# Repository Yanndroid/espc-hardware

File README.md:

# ESP Clock

ESPC stands for [ESP](https://www.espressif.com/) Clock and is a digital IoT clock. It's connected to WiFi, automatically syncs time, shows weather information, and most importantly, has RGB! At its core, there is an ESP8266, and the display is made of WS2812B LEDs.  
It's a project I've been working on over the past few years, and it has allowed me to learn a lot about the C language and PCB designs.

This project consists of multiple repositories:

- [espc-firmware](https://github.com/Yanndroid/espc-firmware)
- espc-hardware
- [espc-python-client](https://github.com/Yanndroid/espc-python-client)
- [espc-dev-tools](https://github.com/Yanndroid/espc-dev-tools)

# ESP Clock Hardware

This repository contains the PCB and 3d models for the ESPC.

### PCB

<div align="center">

</div>

### 3d Models

<div align="center">

</div>

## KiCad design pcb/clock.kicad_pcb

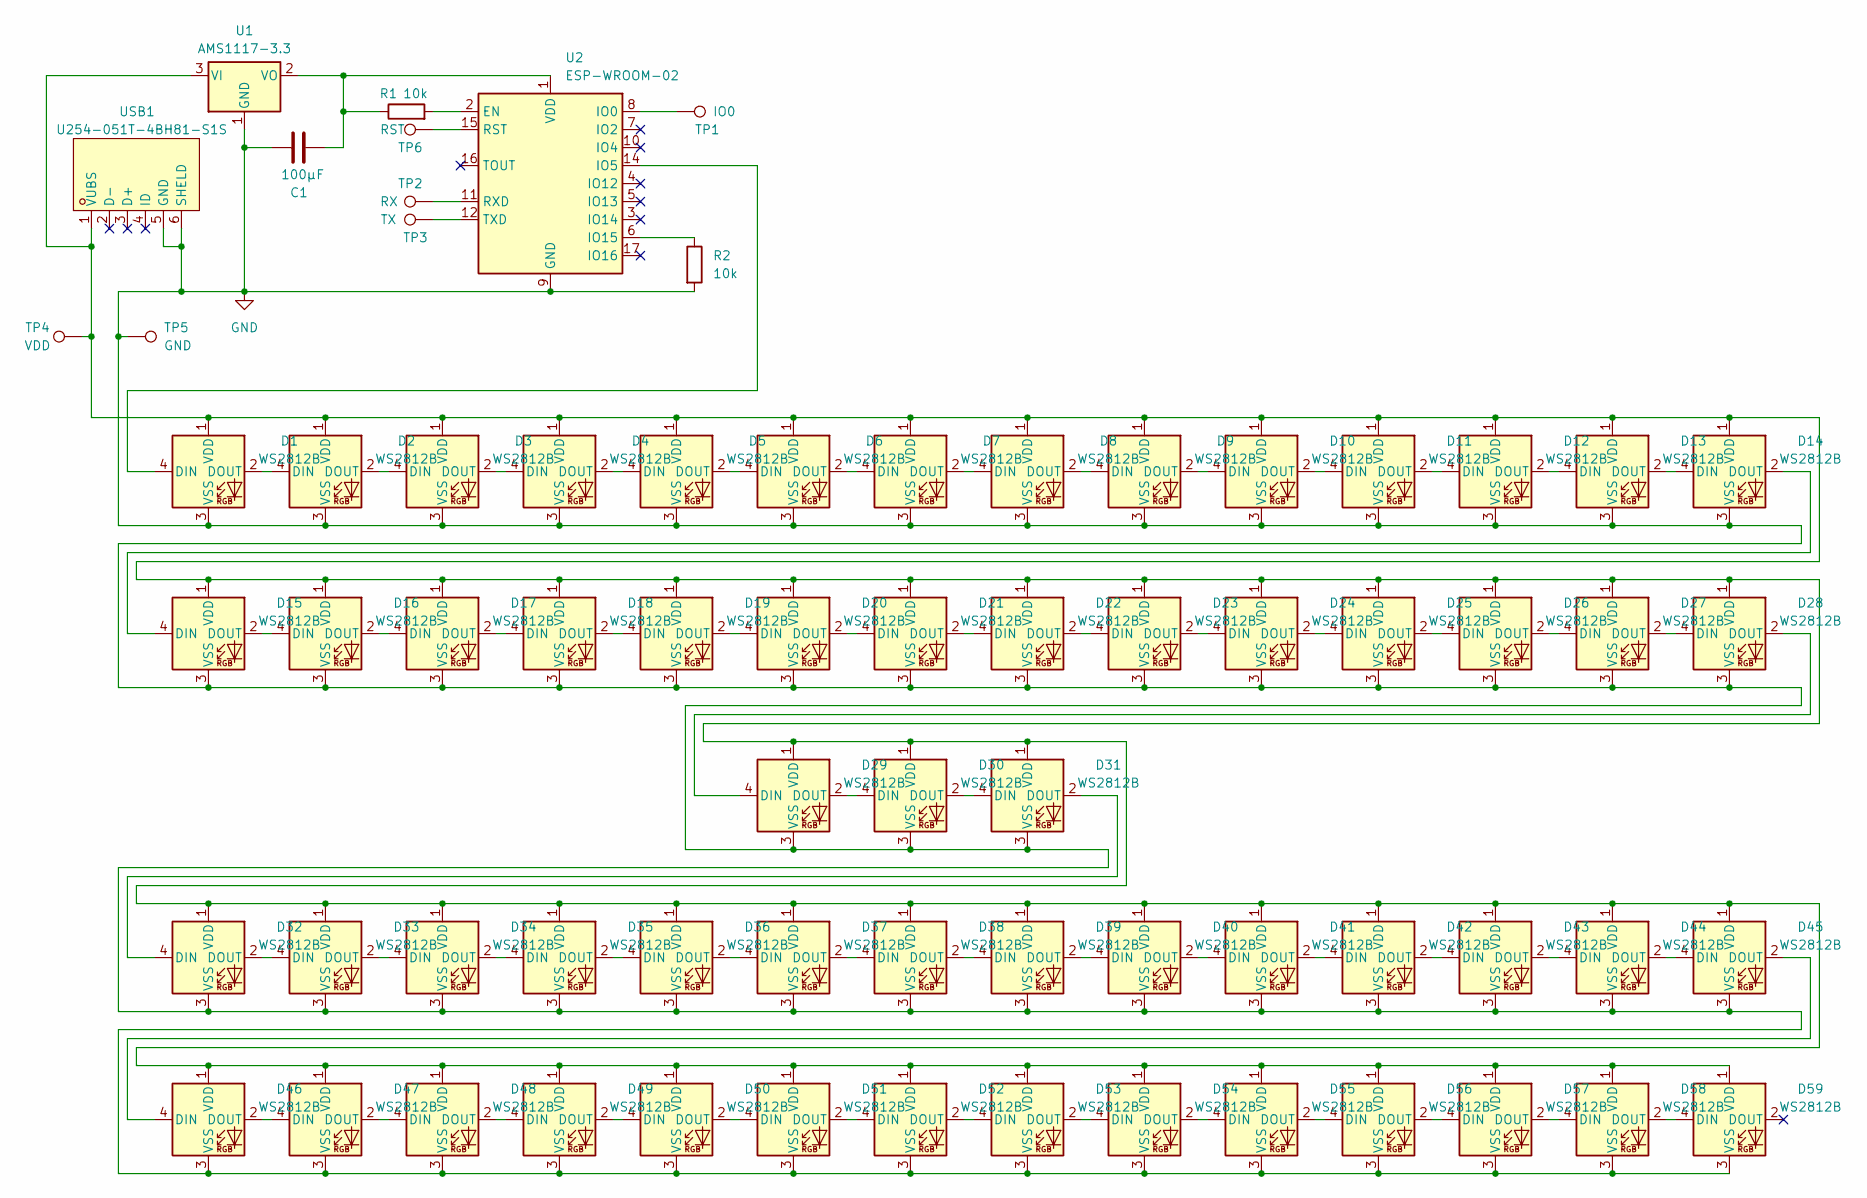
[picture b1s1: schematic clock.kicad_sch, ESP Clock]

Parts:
C1: 100µF; C_1206_3216Metric
D1, D2, D3, D4, D5, D6, D7, D8, D9, D10, D11, D12, D13, D14, D15, D16, D17, D18, D19, D20, D21, D22, D23, D24, D25, D26, D27, D28, D29, D30, D31, D32, D33, D34, D35, D36, D37, D38, D39, D40, D41, D42, D43, D44, D45, D46, D47, D48, D49, D50, D51, D52, D53, D54, D55, D56, D57, D58, D59: WS2812B; LED_WS2812B_PLCC4_5.0x5.0mm_P3.2mm
R1, R2: 10k; R_0603_1608Metric
TP1: IO0; TestPoint_Pad_D1.5mm
TP2: RX; TestPoint_Pad_D1.5mm
TP3: TX; TestPoint_Pad_D1.5mm
TP4: VDD; TestPoint_Pad_D2.5mm
TP5: GND; TestPoint_Pad_D2.5mm
TP6: RST; TestPoint_Pad_D1.5mm
U1: AMS1117-3.3; SOT-223-3_TabPin2
U2: ESP-WROOM-02
USB1: U254-051T-4BH81-S1S; MICRO-USB-SMD_U254-051T-4BH81-S1S; LCSC Part C2682232

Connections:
GND: C1.2, D1.3 (VSS), D2.3 (VSS), D3.3 (VSS), D4.3 (VSS), D5.3 (VSS), D6.3 (VSS), D7.3 (VSS), D8.3 (VSS), D9.3 (VSS), D10.3 (VSS), D11.3 (VSS), D12.3 (VSS), D13.3 (VSS), D14.3 (VSS), D15.3 (VSS), D16.3 (VSS), D17.3 (VSS), D18.3 (VSS), D19.3 (VSS), D20.3 (VSS), D21.3 (VSS), D22.3 (VSS), D23.3 (VSS), D24.3 (VSS), D25.3 (VSS), D26.3 (VSS), D27.3 (VSS), D28.3 (VSS), D29.3 (VSS), D30.3 (VSS), D31.3 (VSS), D32.3 (VSS), D33.3 (VSS), D34.3 (VSS), D35.3 (VSS), D36.3 (VSS), D37.3 (VSS), D38.3 (VSS), D39.3 (VSS), D40.3 (VSS), D41.3 (VSS), D42.3 (VSS), D43.3 (VSS), D44.3 (VSS), D45.3 (VSS), D46.3 (VSS), D47.3 (VSS), D48.3 (VSS), D49.3 (VSS), D50.3 (VSS), D51.3 (VSS), D52.3 (VSS), D53.3 (VSS), D54.3 (VSS), D55.3 (VSS), D56.3 (VSS), D57.3 (VSS), D58.3 (VSS), D59.3 (VSS), R2.2, TP5.1, U1.1 (GND), U2.9 (GND), U2.13 (GND), U2.18 (GND), U2.19 (GND), USB1.5 (GND), USB1.6 (SHELD)
unnamed: D1.4 (DIN), U2.14 (IO5)
unnamed: D1.2 (DOUT), D2.4 (DIN)
unnamed: D1.1 (VDD), D2.1 (VDD), D3.1 (VDD), D4.1 (VDD), D5.1 (VDD), D6.1 (VDD), D7.1 (VDD), D8.1 (VDD), D9.1 (VDD), D10.1 (VDD), D11.1 (VDD), D12.1 (VDD), D13.1 (VDD), D14.1 (VDD), D15.1 (VDD), D16.1 (VDD), D17.1 (VDD), D18.1 (VDD), D19.1 (VDD), D20.1 (VDD), D21.1 (VDD), D22.1 (VDD), D23.1 (VDD), D24.1 (VDD), D25.1 (VDD), D26.1 (VDD), D27.1 (VDD), D28.1 (VDD), D29.1 (VDD), D30.1 (VDD), D31.1 (VDD), D32.1 (VDD), D33.1 (VDD), D34.1 (VDD), D35.1 (VDD), D36.1 (VDD), D37.1 (VDD), D38.1 (VDD), D39.1 (VDD), D40.1 (VDD), D41.1 (VDD), D42.1 (VDD), D43.1 (VDD), D44.1 (VDD), D45.1 (VDD), D46.1 (VDD), D47.1 (VDD), D48.1 (VDD), D49.1 (VDD), D50.1 (VDD), D51.1 (VDD), D52.1 (VDD), D53.1 (VDD), D54.1 (VDD), D55.1 (VDD), D56.1 (VDD), D57.1 (VDD), D58.1 (VDD), D59.1 (VDD), TP4.1, U1.3 (VI), USB1.1 (VUBS)
unnamed: D2.2 (DOUT), D3.4 (DIN)
unnamed: D3.2 (DOUT), D4.4 (DIN)
unnamed: D4.2 (DOUT), D5.4 (DIN)
unnamed: D5.2 (DOUT), D6.4 (DIN)
unnamed: D6.2 (DOUT), D7.4 (DIN)
unnamed: D7.2 (DOUT), D8.4 (DIN)
unnamed: D8.2 (DOUT), D9.4 (DIN)
unnamed: D9.2 (DOUT), D10.4 (DIN)
unnamed: D10.2 (DOUT), D11.4 (DIN)
unnamed: D11.2 (DOUT), D12.4 (DIN)
unnamed: D12.2 (DOUT), D13.4 (DIN)
unnamed: D13.2 (DOUT), D14.4 (DIN)
unnamed: D14.2 (DOUT), D15.4 (DIN)
unnamed: D15.2 (DOUT), D16.4 (DIN)
unnamed: D16.2 (DOUT), D17.4 (DIN)
unnamed: D17.2 (DOUT), D18.4 (DIN)
unnamed: D18.2 (DOUT), D19.4 (DIN)
unnamed: D19.2 (DOUT), D20.4 (DIN)
unnamed: D20.2 (DOUT), D21.4 (DIN)
unnamed: D21.2 (DOUT), D22.4 (DIN)
unnamed: D22.2 (DOUT), D23.4 (DIN)
unnamed: D23.2 (DOUT), D24.4 (DIN)
unnamed: D24.2 (DOUT), D25.4 (DIN)
unnamed: D25.2 (DOUT), D26.4 (DIN)
unnamed: D26.2 (DOUT), D27.4 (DIN)
unnamed: D27.2 (DOUT), D28.4 (DIN)
unnamed: D28.2 (DOUT), D29.4 (DIN)
unnamed: D29.2 (DOUT), D30.4 (DIN)
unnamed: D30.2 (DOUT), D31.4 (DIN)
unnamed: D31.2 (DOUT), D32.4 (DIN)
unnamed: D32.2 (DOUT), D33.4 (DIN)
unnamed: D33.2 (DOUT), D34.4 (DIN)
unnamed: D34.2 (DOUT), D35.4 (DIN)
unnamed: D35.2 (DOUT), D36.4 (DIN)
unnamed: D36.2 (DOUT), D37.4 (DIN)
unnamed: D37.2 (DOUT), D38.4 (DIN)
unnamed: D38.2 (DOUT), D39.4 (DIN)
unnamed: D39.2 (DOUT), D40.4 (DIN)
unnamed: D40.2 (DOUT), D41.4 (DIN)
unnamed: D41.2 (DOUT), D42.4 (DIN)
unnamed: D42.2 (DOUT), D43.4 (DIN)
unnamed: D43.2 (DOUT), D44.4 (DIN)
unnamed: D44.2 (DOUT), D45.4 (DIN)
unnamed: D45.2 (DOUT), D46.4 (DIN)
unnamed: D46.2 (DOUT), D47.4 (DIN)
unnamed: D47.2 (DOUT), D48.4 (DIN)
unnamed: D48.2 (DOUT), D49.4 (DIN)
unnamed: D49.2 (DOUT), D50.4 (DIN)
unnamed: D50.2 (DOUT), D51.4 (DIN)
unnamed: D51.2 (DOUT), D52.4 (DIN)
unnamed: D52.2 (DOUT), D53.4 (DIN)
unnamed: D53.2 (DOUT), D54.4 (DIN)
unnamed: D54.2 (DOUT), D55.4 (DIN)
unnamed: D55.2 (DOUT), D56.4 (DIN)
unnamed: D56.2 (DOUT), D57.4 (DIN)
unnamed: D57.2 (DOUT), D58.4 (DIN)
unnamed: D58.2 (DOUT), D59.4 (DIN)
unnamed: C1.1, R1.1, U1.2 (VO), U2.1 (VDD)
unnamed: R1.2, U2.2 (EN)
unnamed: TP1.1, U2.8 (IO0)
unnamed: R2.1, U2.6 (IO15)
unnamed: TP6.1, U2.15 (RST)
unnamed: TP2.1, U2.11 (RXD)
unnamed: TP3.1, U2.12 (TXD)

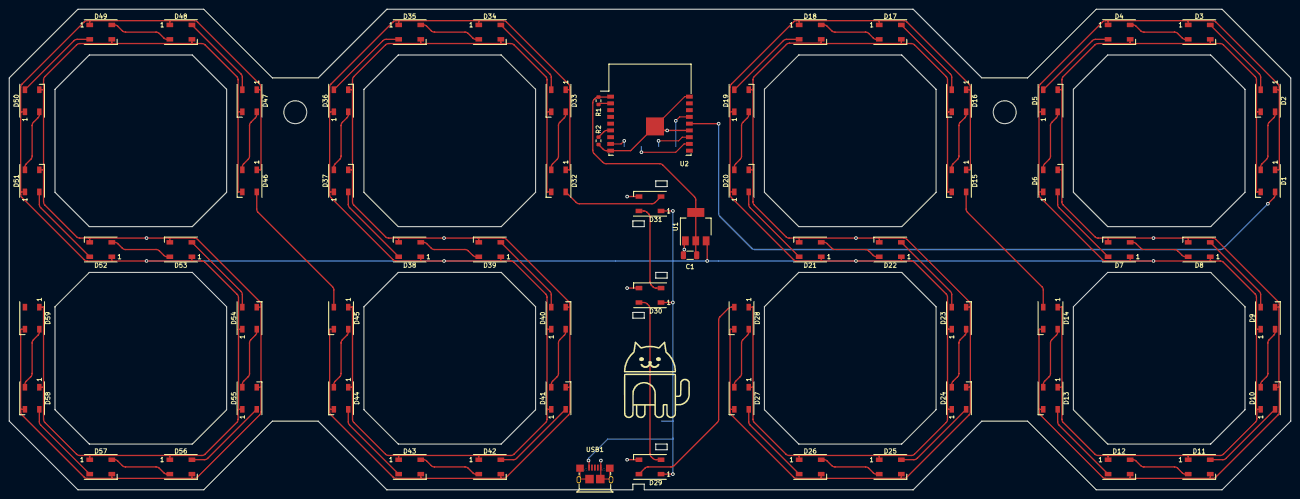
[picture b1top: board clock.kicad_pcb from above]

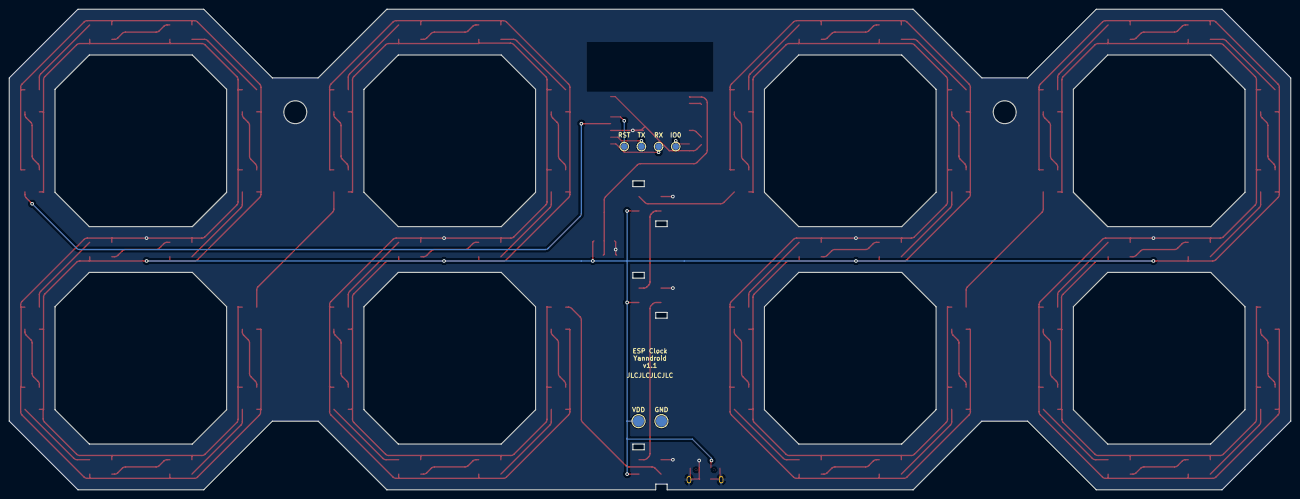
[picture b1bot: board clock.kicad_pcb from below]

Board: 2 copper layers, 284.5 x 106.7 mm, 72 parts (6 on the bottom side), 68 nets.

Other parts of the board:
 : LOGO

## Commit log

2024-06-10 add repo info
